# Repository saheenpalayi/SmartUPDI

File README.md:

# SmartUPDI

SmartUPDI is an open hardware UPDI programmer and USART adapter for modern AVR microcontrollers. It can switch between programming mode and serial communication with the target device, making it useful for both firmware development and serial debugging.

## Project Report

This repository contains the design files and manufacturing outputs for SmartUPDI. It includes a modified revision of the original Version 1 design. Version 1 was assembled and tested as a working prototype, and the modified revision addresses the known Version 1 issues.

### Features

- UPDI programming for supported AVR microcontrollers
- Switchable connection to the target device's USART interface
- One tool for programming and serial communication during development
- Four to five alternative output connector options for different target hardware setups
- KiCad schematic and PCB source files included
- Gerber manufacturing files included

### Modified Revision

The modified version in this repository improves on the original Version 1 hardware. The previously reported LED issues and macOS automatic switching issue have been resolved in this revision.

The board also provides four to five different output connector options. Users can select the connector arrangement that best suits their target hardware and solder the required connector option during assembly.

### Compatibility And Testing

SmartUPDI has been tested with:

- Linux
- Windows
- Arduino projects using the latest MegaTinyCore
- ATtiny AVR 1-series devices
- AVR128DB-series devices, including AVR128DB-family targets

The original Version 1 prototype worked correctly on Linux and Windows, but had LED issues and problems with automatic switching on macOS. These issues have been addressed in the modified revision contained in this repository.

### Original Version 1.0

## Repository Contents

- `Design Files/` - KiCad project, schematic, PCB layout, and project settings
- `Gerber Files/` - fabrication outputs for manufacturing the PCB
- `Media/` - project and assembled-board photographs

## Building Your Own

Anyone may manufacture SmartUPDI for personal use, education, experimentation, or integration into their own projects. Review the schematic, PCB layout, and Gerber files before fabrication, and verify the board against your own target hardware and power requirements.

## Usage And Distribution Policy

You may build, modify, and use SmartUPDI as needed. Reselling the SmartUPDI project, assembled boards, or kits based on this design is prohibited without the author's permission.

This project is provided as-is. Hardware assembly and use are performed at your own risk. Always confirm voltage levels, wiring, and target-device connections before programming.

## License

See [LICENSE](LICENSE) for the license currently included with this repository. The author's intended project policy is that anyone may build and use SmartUPDI, but resale is prohibited. Because the included CC0 text permits commercial redistribution, the license file should be replaced with a license that explicitly prohibits resale if that restriction must be enforceable.

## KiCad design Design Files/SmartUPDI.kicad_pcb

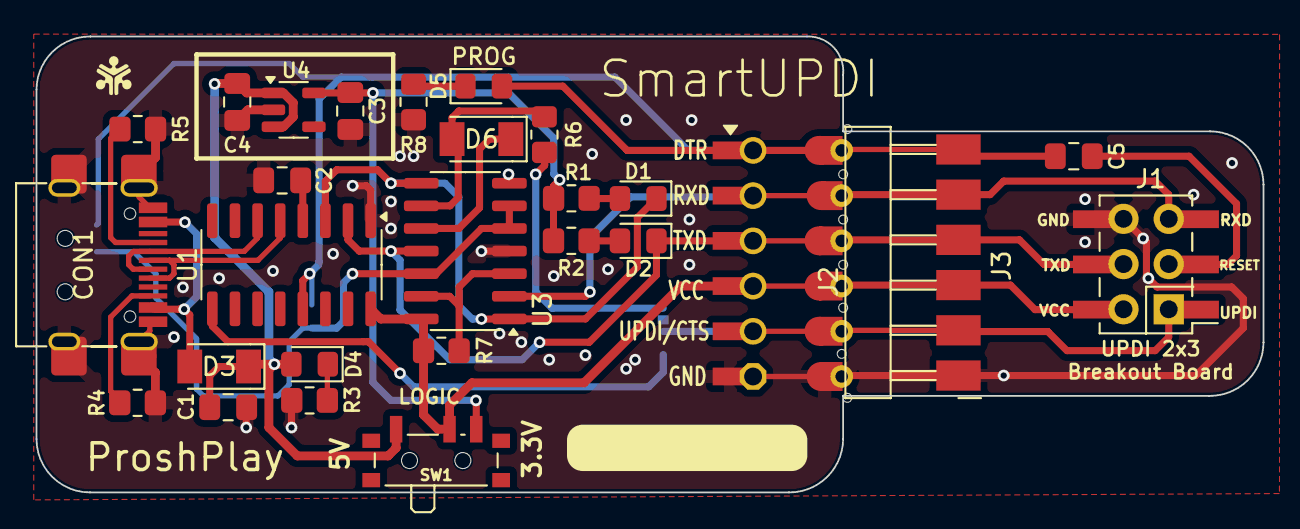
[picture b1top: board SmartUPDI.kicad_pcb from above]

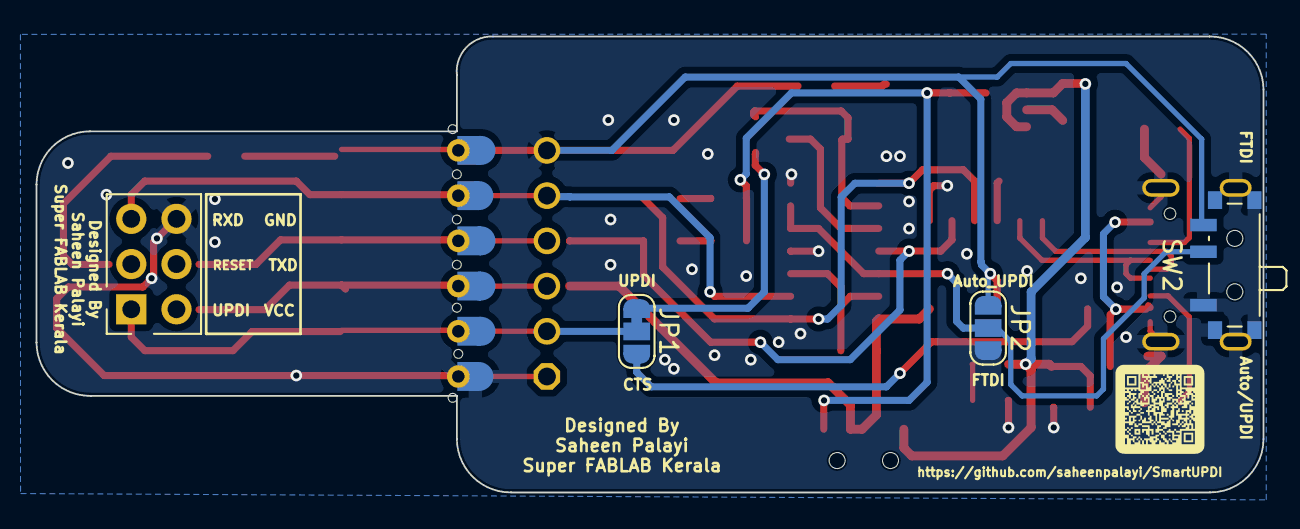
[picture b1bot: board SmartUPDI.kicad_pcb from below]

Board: 2 copper layers, 68.9 x 25.6 mm, 30 parts (3 on the bottom side), 25 nets.

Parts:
C1, C5: 100nF; C_0805_2012Metric_Pad1.18x1.45mm_HandSolder
C2: 10nF; C_0805_2012Metric_Pad1.18x1.45mm_HandSolder
C3, C4: 1uF; C_0805_2012Metric_Pad1.18x1.45mm_HandSolder
CON1: 5077CR-16SMC2-BK-TR; USB_C_Receptacle_G-Switch_GT-USB-7010ASV
D1: RED; LED_0805_2012Metric_Pad1.15x1.40mm_HandSolder
D2, D5: BLUE; LED_0805_2012Metric_Pad1.15x1.40mm_HandSolder
D3: 1A Schottky; Diode_Schottky_MiniSMA
D4: GREEN; LED_0805_2012Metric_Pad1.15x1.40mm_HandSolder
D6: 1N5817 / Schottky 100mA; Diode_Schottky_MiniSMA
J1: PinHeader_02x03_P2.54mm_Vertical_SMD
J2: 1x06 Pin header 2.54 SMD; PinSocket_1x06_P2.54mm_Horizontal_SMD
J3: Conn_PinHeader_FTDI_1x06_P2.54mm_Horizontal_SMD; PinHeader_1x06_P2.54mm_Horizontal_SMD
JP1, JP2: SolderJumper_3_Bridged12; SolderJumper-3_P1.3mm_Bridged12_RoundedPad1.0x1.5mm_NumberL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
R1, R2, R8: 1k; R_0805_2012Metric_Pad1.20x1.40mm_HandSolder
R3: 1K; R_0805_2012Metric_Pad1.20x1.40mm_HandSolder
R4, R5: 5.1k; R_0805_2012Metric_Pad1.20x1.40mm_HandSolder
R6: 499ohm; R_0805_2012Metric_Pad1.20x1.40mm_HandSolder
R7: 10k; R_0805_2012Metric_Pad1.20x1.40mm_HandSolder
SW1, SW2: SW_SPDT; SW_SPDT_PCM12
U1: CH340C; SOIC-16_3.9x9.9mm_P1.27mm
U3: HEF4066BT; SOIC-14_3.9x8.7mm_P1.27mm
U4: AP2112K-3.3; SOT-23-5

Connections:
+3V3: C3.1, R1.1, R2.1, SW1.3 (C), U4.5 (VOUT)
+5V: C1.1, C4.1, D3.1 (K), D4.2 (A), SW1.1 (A), U4.1 (VIN), U4.3 (EN)
Brakeout_UPDI: J1.1, J2.5, J3.2, JP1.2 (C)
CTS: JP1.3 (B), U1.9 (~CTS)
D+: CON1.A6 (DP1), CON1.B6 (DP2), U1.5 (UD+)
D-: CON1.A7 (DN1), CON1.B7 (DN2), U1.6 (UD-)
DTR: C5.1, D5.2 (A), J2.1, J3.6, JP2.1 (A), SW2.3 (C), U1.13 (~DTR)
GND: C1.2, C2.2, C3.2, C4.2, CON1.S1 (Shield), J1.6, J2.6, J3.1, JP2.3 (B), R3.2, R4.2, R5.2, R8.1, SW2.1 (A), U1.1 (GND), U3.4 (2Y), U3.7 (VSS), U4.2 (GND)
MODE-FTDI: R7.1, U3.3 (2Z), U3.13 (1E)
MODE-UPDI: JP2.2 (C), SW2.2 (B), U3.5 (2E), U3.6 (3E), U3.12 (4E)
unnamed: CON1.A5 (CC1), R5.1
unnamed: CON1.B5 (CC2), R4.1
unnamed: D1.2 (A), R1.2
unnamed: D2.2 (A), R2.2
unnamed: D4.1 (K), R3.1
unnamed: D5.1 (K), R8.2
unnamed: D6.2 (A), R6.1, U3.9 (3Z)
unnamed: D6.1 (K), U3.10 (4Z)
unnamed: C5.2, J1.3
unnamed: C2.1, U1.4 (V3)
RX: D1.1 (K), U1.3 (RXD), U3.1 (1Y), U3.8 (3Y)
T-RX: J1.5, J2.2, J3.5, U3.2 (1Z)
TX: D2.1 (K), J1.4, J2.3, J3.4, U1.2 (TXD), U3.11 (4Y)
UPDI: JP1.1 (A), R6.2
VCC: J1.2, J2.4, J3.3, R7.2, SW1.2 (B), U1.16 (VCC), U3.14 (VDD)
